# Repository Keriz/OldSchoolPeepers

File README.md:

# OldSchoolPeepers
OldSchoolPeepers is a 48x48 squared form-factor led panel which streams a camera output in quantified shades of color, inspired by Greg Davill.

The schematic has been programmed in Python using SKiDL.

## Panel close-up view
### Front

 (WIP)
### Back (Not done)

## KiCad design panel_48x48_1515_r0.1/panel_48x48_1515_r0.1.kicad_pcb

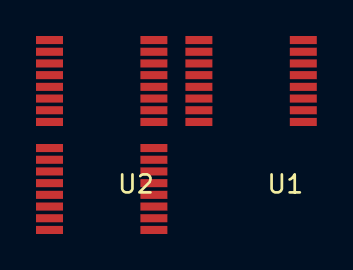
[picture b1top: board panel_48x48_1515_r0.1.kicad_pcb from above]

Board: 2 copper layers, 3 parts (0 on the bottom side), 7 nets, no tracks yet.

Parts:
U1, U2, U3: 74HC595; TSSOP-16_slim

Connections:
CLK: U1.11, U2.11, U3.11
GND: U1.8, U2.8, U3.8
unnamed: U1.9, U2.14
unnamed: U2.9, U3.14
ROW_LATCH: U1.12, U2.12, U3.12
VCC: U1.10, U1.16, U2.10, U2.16, U3.10, U3.16
~ROW_BLANK: U1.13, U2.13, U3.13

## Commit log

2021-08-07 Add diagram for the led panel
2021-08-08 Untrack temporary kicad & skidl files
2021-08-08 Add initial documentation
2021-08-08 Schematic initial draft, using library skidl
2021-08-08 Track the most important file - oops!
2022-05-17 Add pictures of panel
2022-05-17 Mention library name in readme
